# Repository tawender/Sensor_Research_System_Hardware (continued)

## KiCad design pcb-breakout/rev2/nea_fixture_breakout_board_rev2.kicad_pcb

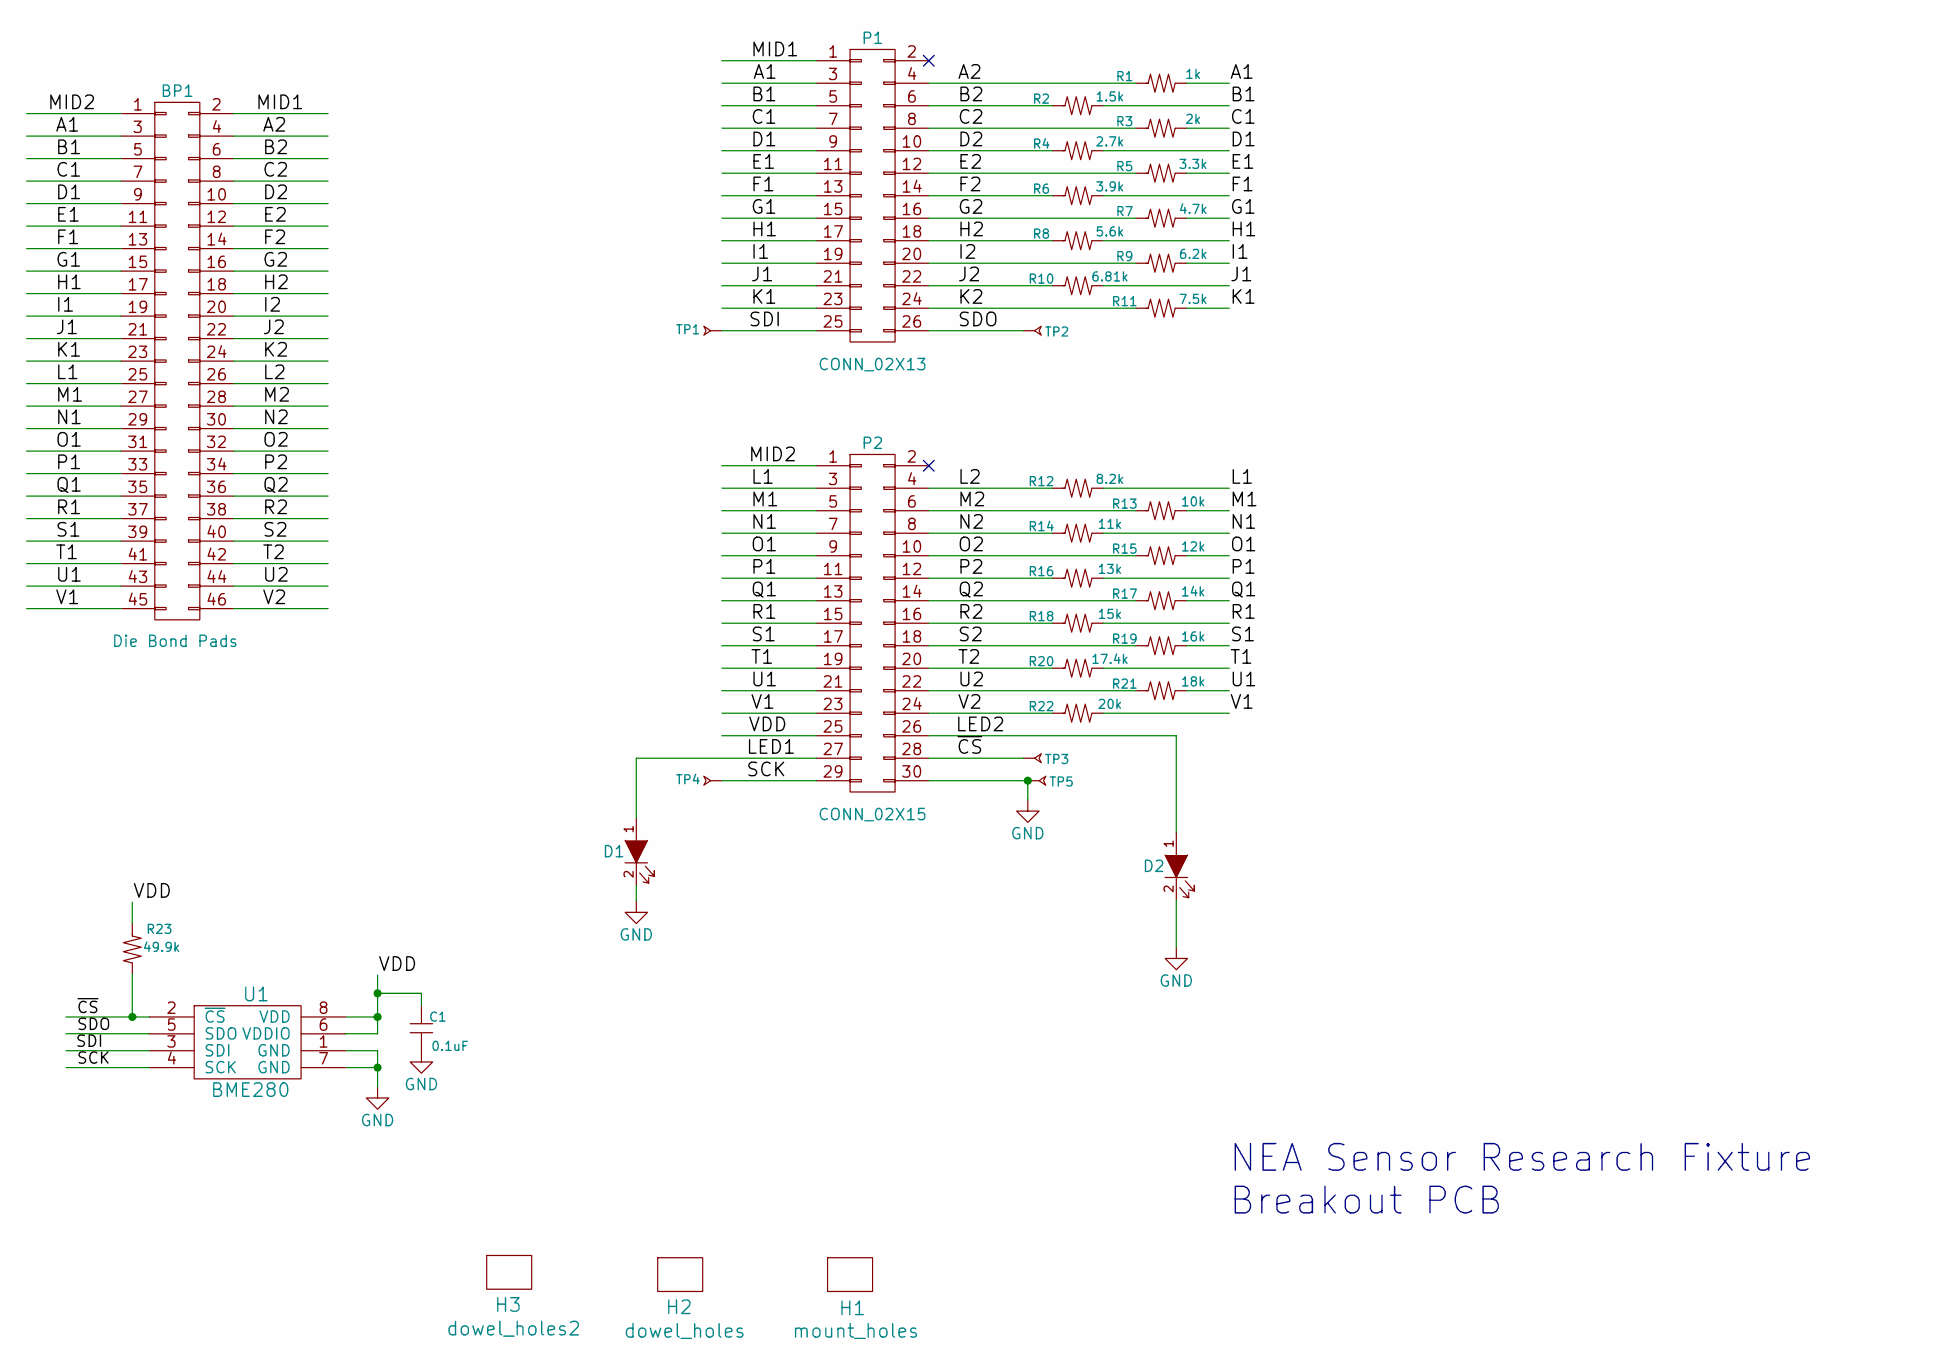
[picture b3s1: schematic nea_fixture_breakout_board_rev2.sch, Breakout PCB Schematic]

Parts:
BP1: Die Bond Pads; bondpads
C1: 0.1uF; R_0603_HandSoldering; manufacturer pn GRM188R71C104KA01D
D1, D2: LED_SMT; 0603_diode; manufacturer pn APT1608SGC
H1: mount_holes
H2: dowel_holes
H3: dowel_holes2
P1: CONN_02X13; header_smt_2x13
P2: CONN_02X15; header_smt_2x15; manufacturer pn 2-146134-1
R1: 1k; R_0603_HandSoldering; manufacturer pn RC0603FR-071KL
R2: 1.5k; R_0603_HandSoldering; manufacturer pn RC0603FR-071K5L
R3: 2k; R_0603_HandSoldering; manufacturer pn RC0603FR-071KL
R4: 2.7k; R_0603_HandSoldering; manufacturer pn RC0603FR-071KL
R5: 3.3k; R_0603_HandSoldering; manufacturer pn RC0603FR-071KL
R6: 3.9k; R_0603_HandSoldering; manufacturer pn RC0603FR-071KL
R7: 4.7k; R_0603_HandSoldering; manufacturer pn RC0603FR-071KL
R8: 5.6k; R_0603_HandSoldering; manufacturer pn RC0603FR-071KL
R9: 6.2k; R_0603_HandSoldering; manufacturer pn RC0603FR-071KL
R10: 6.81k; R_0603_HandSoldering; manufacturer pn RC0603FR-071KL
R11: 7.5k; R_0603_HandSoldering; manufacturer pn RC0603FR-071KL
R12: 8.2k; R_0603_HandSoldering; manufacturer pn RC0603FR-071KL
R13: 10k; R_0603_HandSoldering; manufacturer pn RC0603FR-071KL
R14: 11k; R_0603_HandSoldering; manufacturer pn RC0603FR-071KL
R15: 12k; R_0603_HandSoldering; manufacturer pn RC0603FR-071KL
R16: 13k; R_0603_HandSoldering; manufacturer pn RC0603FR-071KL
R17: 14k; R_0603_HandSoldering; manufacturer pn RC0603FR-071KL
R18: 15k; R_0603_HandSoldering; manufacturer pn RC0603FR-071KL
R19: 16k; R_0603_HandSoldering; manufacturer pn RC0603FR-071KL
R20: 17.4k; R_0603_HandSoldering; manufacturer pn RC0603FR-071KL
R21: 18k; R_0603_HandSoldering; manufacturer pn RC0603FR-071KL
R22: 20k; R_0603_HandSoldering; manufacturer pn RC0603FR-071KL
R23: 49.9k; R_0603_HandSoldering; manufacturer pn RC0603FR-0749K9L
TP1, TP2, TP3, TP4, TP5: TP_wirehole; Header_Pin_Res
U1: BME280; BME280_hand; manufacturer pn BME280

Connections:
/A1: BP1.3, P1.3, R1.1
/A2: BP1.4, P1.4, R1.2
/B1: BP1.5, P1.5, R2.1
/B2: BP1.6, P1.6, R2.2
/C1: BP1.7, P1.7, R3.1
/C2: BP1.8, P1.8, R3.2
/D1: BP1.9, P1.9, R4.1
/D2: BP1.10, P1.10, R4.2
/E1: BP1.11, P1.11, R5.1
/E2: BP1.12, P1.12, R5.2
/F1: BP1.13, P1.13, R6.1
/F2: BP1.14, P1.14, R6.2
/G1: BP1.15, P1.15, R7.1
/G2: BP1.16, P1.16, R7.2
/H1: BP1.17, P1.17, R8.1
/H2: BP1.18, P1.18, R8.2
/I1: BP1.19, P1.19, R9.1
/I2: BP1.20, P1.20, R9.2
/J1: BP1.21, P1.21, R10.1
/J2: BP1.22, P1.22, R10.2
/K1: BP1.23, P1.23, R11.1
/K2: BP1.24, P1.24, R11.2
/L1: BP1.25, P2.3, R12.1
/L2: BP1.26, P2.4, R12.2
/LED1: D1.1 (A), P2.27
/LED2: D2.1 (A), P2.26
/M1: BP1.27, P2.5, R13.1
/M2: BP1.28, P2.6, R13.2
/MID1: BP1.2, P1.1
/MID2: BP1.1, P2.1
/N1: BP1.29, P2.7, R14.1
/N2: BP1.30, P2.8, R14.2
/O1: BP1.31, P2.9, R15.1
/O2: BP1.32, P2.10, R15.2
/P1: BP1.33, P2.11, R16.1
/P2: BP1.34, P2.12, R16.2
/Q1: BP1.35, P2.13, R17.1
/Q2: BP1.36, P2.14, R17.2
/R1: BP1.37, P2.15, R18.1
/R2: BP1.38, P2.16, R18.2
/S1: BP1.39, P2.17, R19.1
/S2: BP1.40, P2.18, R19.2
/SCK: P2.29, TP4.1, U1.4 (SCK)
/SDI: P1.25, TP1.1, U1.3 (SDI)
/SDO: P1.26, TP2.1, U1.5 (SDO)
/T1: BP1.41, P2.19, R20.1
/T2: BP1.42, P2.20, R20.2
/U1: BP1.43, P2.21, R21.1
/U2: BP1.44, P2.22, R21.2
/V1: BP1.45, P2.23, R22.1
/V2: BP1.46, P2.24, R22.2
/VDD: C1.1, P2.25, R23.2, U1.6 (VDDIO), U1.8 (VDD)
/~CS: P2.28, R23.1, TP3.1, U1.2 (~CS)
GND: C1.2, D1.2 (K), D2.2 (K), P2.30, TP5.1, U1.1 (GND), U1.7 (GND)

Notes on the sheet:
NEA Sensor Research Fixture Breakout PCB

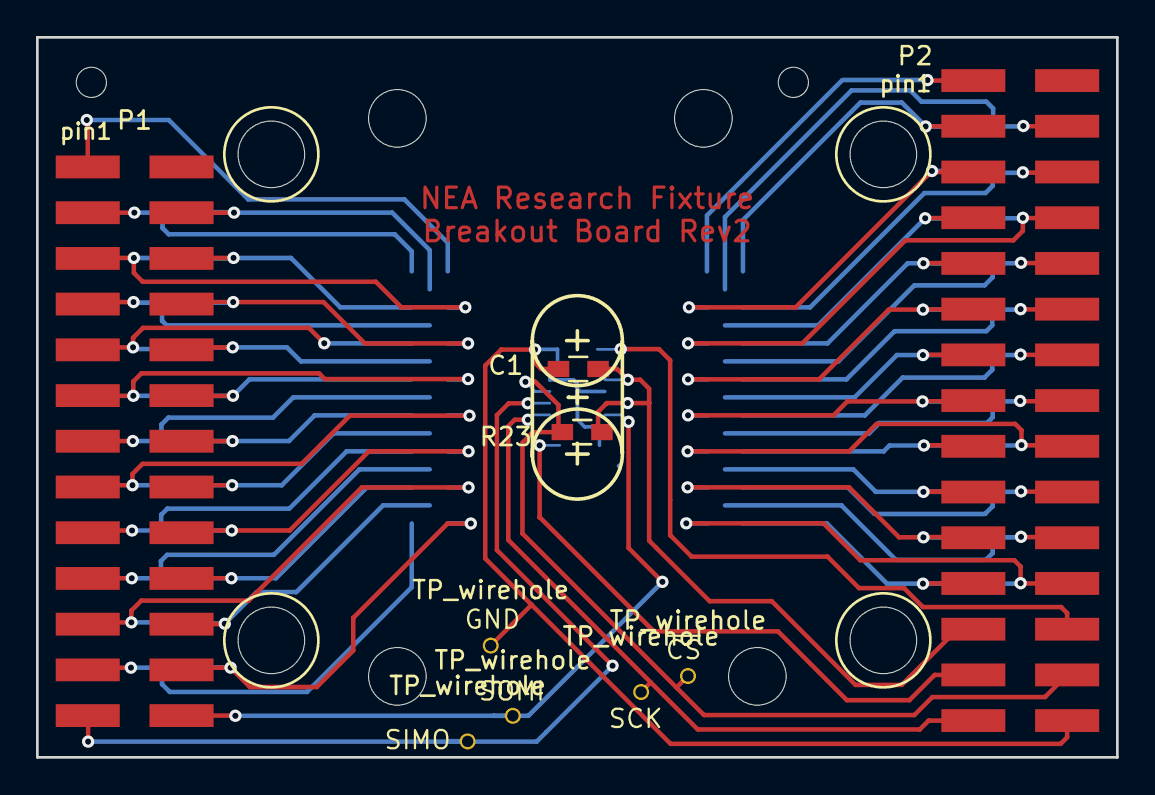
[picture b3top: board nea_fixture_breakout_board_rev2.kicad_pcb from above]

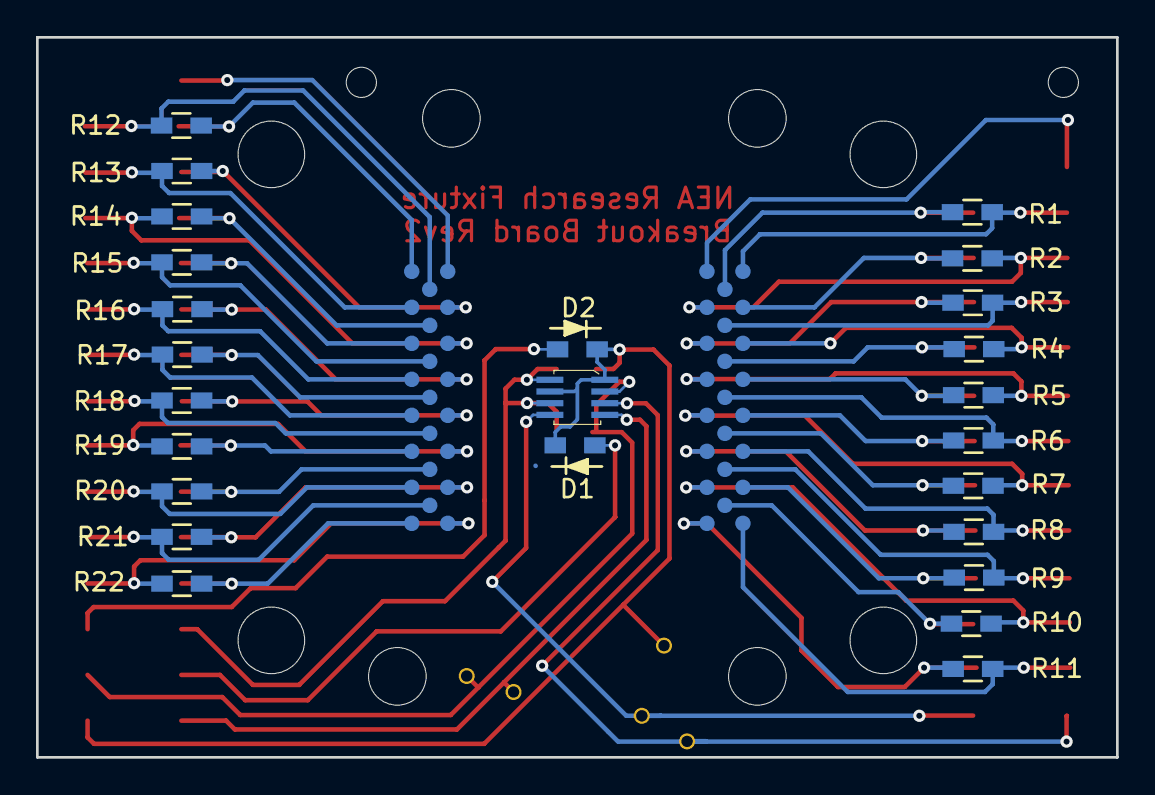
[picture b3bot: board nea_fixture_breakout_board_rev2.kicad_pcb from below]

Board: 2 copper layers, 60.0 x 40.0 mm, 38 parts (26 on the bottom side), 54 nets.

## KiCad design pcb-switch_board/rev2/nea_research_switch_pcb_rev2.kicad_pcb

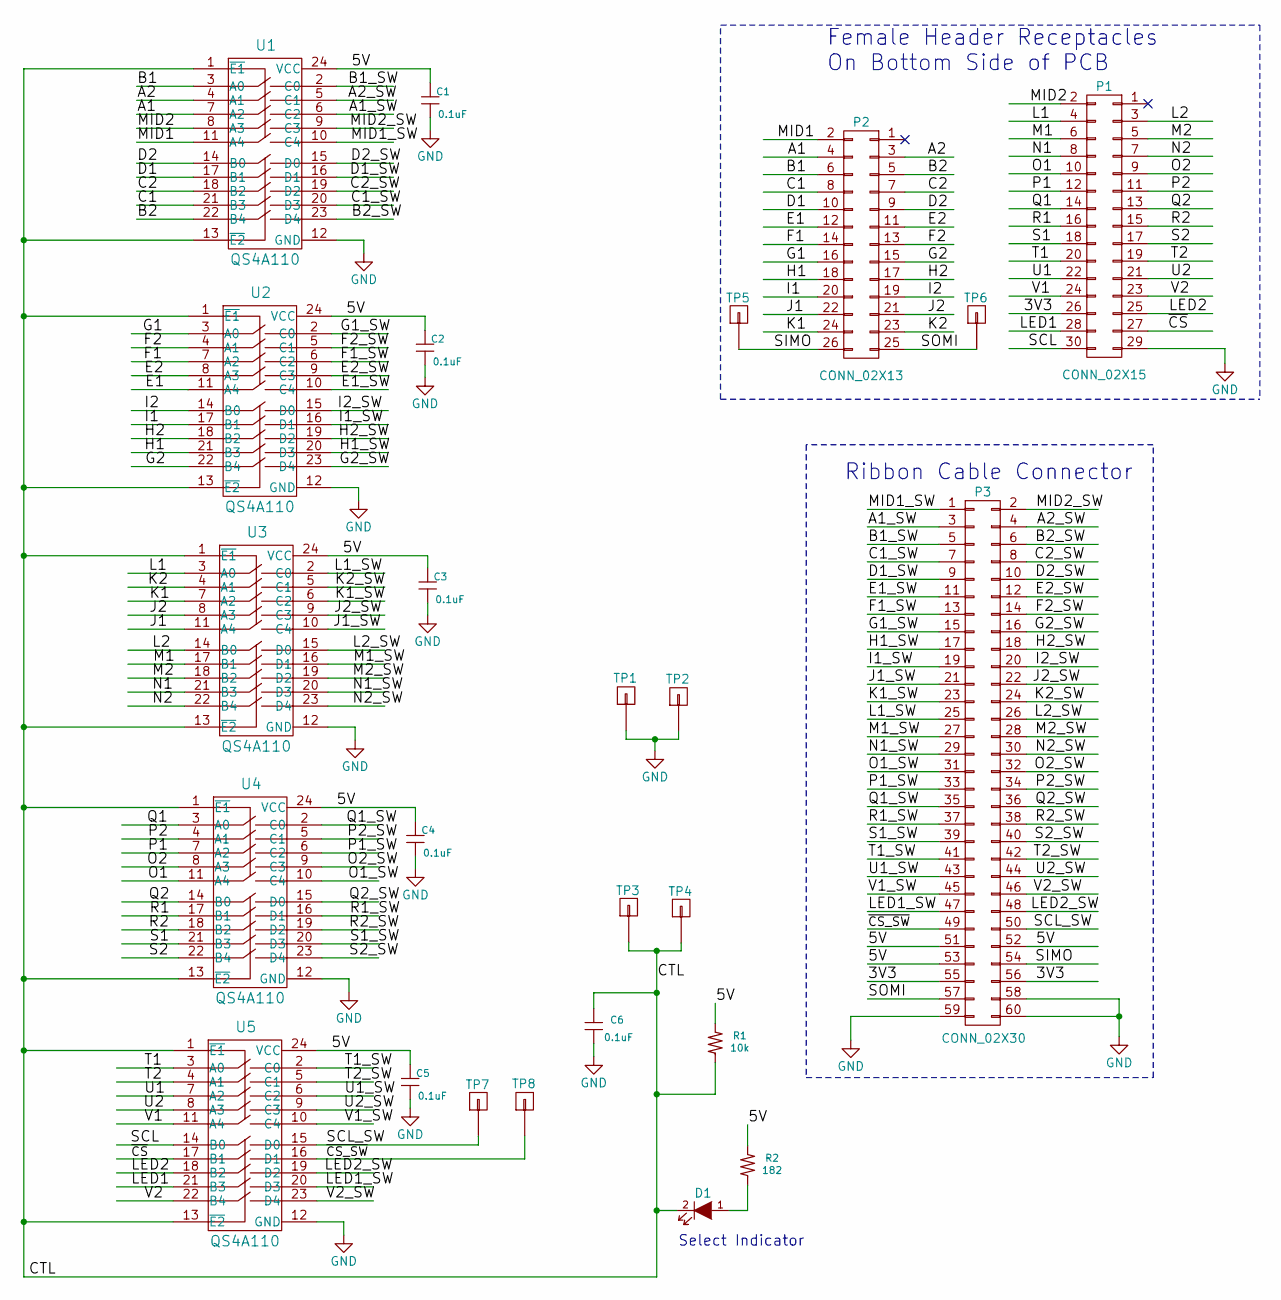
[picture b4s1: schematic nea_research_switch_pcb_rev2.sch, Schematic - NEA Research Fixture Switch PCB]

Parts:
C1, C2, C3, C4, C5, C6: 0.1uF; 0402; manufacturer pn 0402YD104KAT2A
D1: LED_SMT; 0603-D; manufacturer pn APT1608SGC
P1: CONN_02X15; Pin_Header_Straight_2x15_Pitch2.54mm; manufacturer pn 2-146134-1
P2: CONN_02X13; Pin_Header_Straight_2x13_Pitch2.54mm; manufacturer pn 1-534998-5
P3: CONN_02X30; HDR_2x30_F_latch; manufacturer pn 1-5499922-1
R1: 10k; 0603; manufacturer pn RC0603FR-0710KL
R2: 182; 0603; manufacturer pn RC0603FR-07182RL
TP1, TP2, TP3, TP4, TP5, TP6, TP7, TP8: header_pin; Header_Pin_Rnd
U1, U2, U3, U4, U5: QS4A110; QSOP-24; manufacturer pn QS4A110QG

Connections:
/3V3: P1.26, P3.55, P3.56
/5V: C1.1, C2.1, C3.1, C4.1, C5.1, P3.51, P3.52, P3.53, R1.1, R2.1, U1.24 (VCC), U2.24 (VCC), U3.24 (VCC), U4.24 (VCC), U5.24 (VCC)
/A1: P2.4, U1.7 (A2)
/A1_SW: P3.3, U1.6 (C2)
/A2: P2.3, U1.4 (A1)
/A2_SW: P3.4, U1.5 (C1)
/B1: P2.6, U1.3 (A0)
/B1_SW: P3.5, U1.2 (C0)
/B2: P2.5, U1.22 (B4)
/B2_SW: P3.6, U1.23 (D4)
/C1: P2.8, U1.21 (B3)
/C1_SW: P3.7, U1.20 (D3)
/C2: P2.7, U1.18 (B2)
/C2_SW: P3.8, U1.19 (D2)
/CTL: C6.1, D1.2 (K), R1.2, TP3.1, TP4.1, U1.1 (~E1), U1.13 (~E2), U2.1 (~E1), U2.13 (~E2), U3.1 (~E1), U3.13 (~E2), U4.1 (~E1), U4.13 (~E2), U5.1 (~E1), U5.13 (~E2)
/D1: P2.10, U1.17 (B1)
/D1_SW: P3.9, U1.16 (D1)
/D2: P2.9, U1.14 (B0)
/D2_SW: P3.10, U1.15 (D0)
/E1: P2.12, U2.11 (A4)
/E1_SW: P3.11, U2.10 (C4)
/E2: P2.11, U2.8 (A3)
/E2_SW: P3.12, U2.9 (C3)
/F1: P2.14, U2.7 (A2)
/F1_SW: P3.13, U2.6 (C2)
/F2: P2.13, U2.4 (A1)
/F2_SW: P3.14, U2.5 (C1)
/G1: P2.16, U2.3 (A0)
/G1_SW: P3.15, U2.2 (C0)
/G2: P2.15, U2.22 (B4)
/G2_SW: P3.16, U2.23 (D4)
/H1: P2.18, U2.21 (B3)
/H1_SW: P3.17, U2.20 (D3)
/H2: P2.17, U2.18 (B2)
/H2_SW: P3.18, U2.19 (D2)
/I1: P2.20, U2.17 (B1)
/I1_SW: P3.19, U2.16 (D1)
/I2: P2.19, U2.14 (B0)
/I2_SW: P3.20, U2.15 (D0)
/J1: P2.22, U3.11 (A4)
/J1_SW: P3.21, U3.10 (C4)
/J2: P2.21, U3.8 (A3)
/J2_SW: P3.22, U3.9 (C3)
/K1: P2.24, U3.7 (A2)
/K1_SW: P3.23, U3.6 (C2)
/K2: P2.23, U3.4 (A1)
/K2_SW: P3.24, U3.5 (C1)
/L1: P1.4, U3.3 (A0)
/L1_SW: P3.25, U3.2 (C0)
/L2: P1.3, U3.14 (B0)
/L2_SW: P3.26, U3.15 (D0)
/LED1: P1.28, U5.21 (B3)
/LED1_SW: P3.47, U5.20 (D3)
/LED2: P1.25, U5.18 (B2)
/LED2_SW: P3.48, U5.19 (D2)
/M1: P1.6, U3.17 (B1)
/M1_SW: P3.27, U3.16 (D1)
/M2: P1.5, U3.18 (B2)
/M2_SW: P3.28, U3.19 (D2)
/MID1: P2.2, U1.11 (A4)
/MID1_SW: P3.1, U1.10 (C4)
/MID2: P1.2, U1.8 (A3)
/MID2_SW: P3.2, U1.9 (C3)
/N1: P1.8, U3.21 (B3)
/N1_SW: P3.29, U3.20 (D3)
/N2: P1.7, U3.22 (B4)
/N2_SW: P3.30, U3.23 (D4)
/O1: P1.10, U4.11 (A4)
/O1_SW: P3.31, U4.10 (C4)
/O2: P1.9, U4.8 (A3)
/O2_SW: P3.32, U4.9 (C3)
/P1: P1.12, U4.7 (A2)
/P1_SW: P3.33, U4.6 (C2)
/P2: P1.11, U4.4 (A1)
/P2_SW: P3.34, U4.5 (C1)
/Q1: P1.14, U4.3 (A0)
/Q1_SW: P3.35, U4.2 (C0)
/Q2: P1.13, U4.14 (B0)
/Q2_SW: P3.36, U4.15 (D0)
/R1: P1.16, U4.17 (B1)
/R1_SW: P3.37, U4.16 (D1)
/R2: P1.15, U4.18 (B2)
/R2_SW: P3.38, U4.19 (D2)
/S1: P1.18, U4.21 (B3)
/S1_SW: P3.39, U4.20 (D3)
/S2: P1.17, U4.22 (B4)
/S2_SW: P3.40, U4.23 (D4)
/SCL: P1.30, U5.14 (B0)
/SCL_SW: P3.50, TP7.1, U5.15 (D0)
/SIMO: P2.26, P3.54, TP5.1
/SOMI: P2.25, P3.57, TP6.1
/T1: P1.20, U5.3 (A0)
/T1_SW: P3.41, U5.2 (C0)
/T2: P1.19, U5.4 (A1)
/T2_SW: P3.42, U5.5 (C1)
/U1: P1.22, U5.7 (A2)
/U1_SW: P3.43, U5.6 (C2)
/U2: P1.21, U5.8 (A3)
/U2_SW: P3.44, U5.9 (C3)
/V1: P1.24, U5.11 (A4)
/V1_SW: P3.45, U5.10 (C4)
/V2: P1.23, U5.22 (B4)
/V2_SW: P3.46, U5.23 (D4)
/~CS: P1.27, U5.17 (B1)
/~CS_SW: P3.49, TP8.1, U5.16 (D1)
GND: C1.2, C2.2, C3.2, C4.2, C5.2, C6.2, P1.29, P3.58, P3.59, P3.60, TP1.1, TP2.1, U1.12 (GND), U2.12 (GND), U3.12 (GND), U4.12 (GND), U5.12 (GND)
unnamed: D1.1 (A), R2.2

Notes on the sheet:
Female Header Receptacles On Bottom Side of PCB
Ribbon Cable Connector
Select Indicator

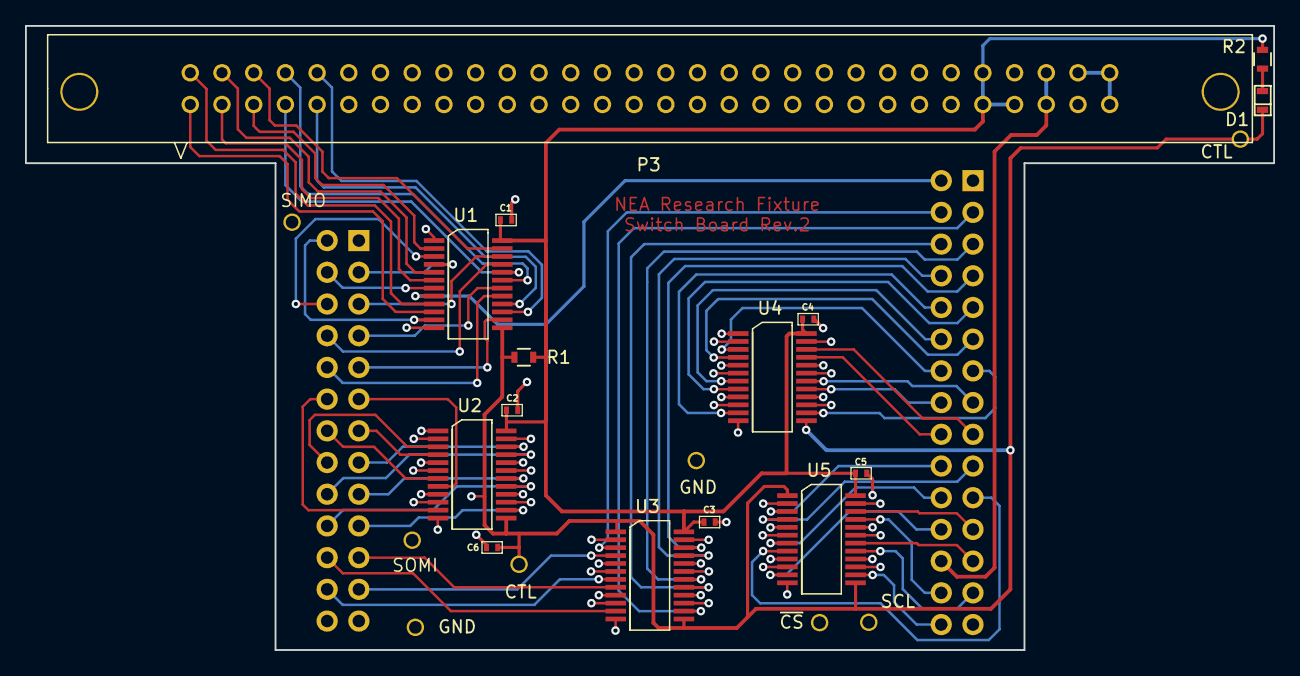
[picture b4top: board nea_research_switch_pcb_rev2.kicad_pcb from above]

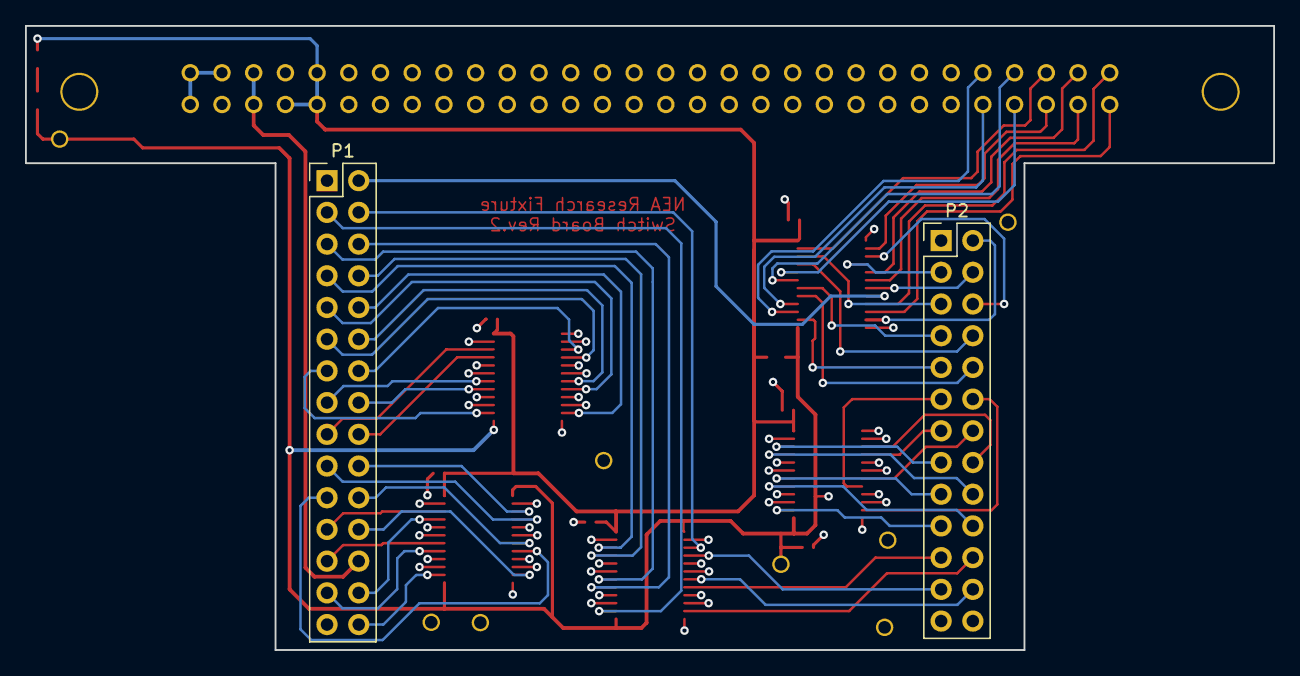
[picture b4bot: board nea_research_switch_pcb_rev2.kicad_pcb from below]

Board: 4 copper layers, 100.0 x 50.0 mm, 25 parts (2 on the bottom side), 107 nets.

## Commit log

2017-01-11 Initial commit for test fixture using reduced size pcb, oval PHT sensor cutout
2017-01-12 before swapping headers/pcb mounting holes, -no changes to keying method yet
2017-01-13 -widened pcb -moved headers to outside edges of board -moved mounting screws to inside of headers -changed size of probe block to match pcb size
2017-01-14 -increased die size -cut probe block in half (probe_block_top, probe_block_bot)
2017-01-17 -changed dowel pins to 1/8
2017-01-17 -changed dowel pins to 1/8 inch -changed die size to 21.5mm wide by 17mm high(got rid of text at bottom) -updated probe block which was cut in half(top and bottom section) -fixture assembly constrain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
2017-01-18 -saved a copy of probe_block_bot to 'another_name' and that allowed the assembly to accept constraints to assemble the fixture pieces -updated die_holder_block to match the increased size of the pcb,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
2017-01-19 -renamed file another_name.FCStd to probe_block_bot_.FCStd > -used renamed file to fix test fixture assembly NEA_research_fixture_R2
2017-01-20 -increased width of all blocks to accomodate thumbscrews for clamping -added thumbscrews and threaded inserts to the fixture assembly
2017-01-21 -increased size of blocks slightly to be larger than pcb outline -removed gas inlet/outlet holes in the probe_block_top and probe_block_bot files -added new files probe_block_bot_gas and probe_block_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
2017-01-21 -fixed tweezer pocket in die_holder_block to reach to the edge of the part
2017-01-24 completed schematic and layout for breakout pcb
2017-01-25 -updated schematic with unique resistor values at each sensor location -created pdfs of the schematic and pcb layout
2017-01-26 -reorganized directory structure -created new directory for pcb used to connect sensors to adc and take measurements
2017-01-26 -starting on measurement pcb
2017-02-04 --fixed breakout pcb drill file for reorder and regenerated gerbers --
2017-02-08 -added directory and project files for switch pcb / measurement pcb -schematic for switch pcb is created -beginning to lay out switch pcb
2017-02-08 -laying out switch board
2017-02-09 -progress on switch board layout
2017-02-10 -finished rev1 of switch board layout -zip file sent off for pcb order
2017-02-15 -fixture probe blocks added secondary dowel pin holes to align independant of die holding block-added a relief around perimeter of die in the die holding block -tightened dowel holes in die holding b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
2017-02-15 -saved probe_block_top_gas
2017-02-18 -revised breakout board to use BME280 sensor for SPI instead of I2C -revised switch board to accomodate SPI bus(2 extra signals) -added SPI bus testpoints to both boards -organized breakout and switc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
2017-02-21 -removed solder paste layer from breakout board bond pad footprint -starting on control board schematic
2017-02-21 -adding invoices for spring probes, stencil
2017-02-22 -updated 3d model of manufacturing fixture with new mechanical parts for base mounted dowel pins -added 3d model of fixture used for gas testing
2017-02-22 -added adc mux and gnd mux to control board schematic
2017-02-24 -updated wiring diagram for breakout board and switch board headers -fixed switch board schematic pdf naming
2017-04-08 -changed die_holder_block depth from 41mm to 40mm -added a probe block that is a one-piece design thick enough to hold spring probes
2017-04-22 -working on new pcb for research test fixture that will sit on top of the breakout board headers. This new pcb will use an msp430 to control measurements at each sensor and will communicate with a ra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
2017-04-26 -schematic is being refined -working on placement of pcb parts -all footprints are completed
2017-04-27 -component placement completed -routing just started
2017-04-28 -replaced all measurement board 0402 components with 0603 -adjusted placement and started routing on the layout
2017-04-29 -updated current measurement spreadsheet
2017-05-04 -more progress on the measurement board layout
2017-05-05 progress on the measurement board layout
2017-05-08 -nearing completion of measurement board layout -routed most signal traces, just need to add testpoints and fix DRC voilations -changed MSP430 programming connector from 2x7 header to 10-pin flex cab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
2017-05-09 -layout of measurement board completed -gerber files created -added a pdf of the schematic
2017-07-20 -added BOM and files for measurement board assembly house
